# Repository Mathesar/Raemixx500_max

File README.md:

# Rämixx500_MAX

Rämixx500_MAX is an enhanced version of Sukkoperra's [Rämixx500](https://github.com/SukkoPera/Raemixx500), an Open Hardware remake of the Commodore Amiga 500+ mainboard, revision 8A.1.

## Features
The main feature of the Rämixx500_MAX compared to the original Rämixx500 is more RAM in the form of a 72pins 4Meg SIMM module that gives the Rämixx500_MAX 2Meg CHIP + 1.5Meg SLOW ram. Good working SIMM modules are much easier to source and more reliable than the DIP chips that were originally used in the A500+.

3.5 Megabytes of RAM is the maximum amount an A500+ can use without attaching an accelerator, hence the name Rämixx500_**MAX**.

All the new features of the Rämixx500_MAX are:

* **3.5 Megabytes of RAM**: Using a 72pin SIMM that is at least 4Meg in size.
* **Improved ESD Protection for the Joystick Ports**: The Rämixx500_MAX protects just the lines that go into the sensitive CIA and Paula chips but these lines are more rigorously protected by placing the ESD diodes right at the connectors.
* **Improved Hard Disk LED support**: This version accepts both active high and active low harddisk activity signals. Note that the active low harddisk activity LED input is only compatible with 5V devices. The active high harddisk activity LED input is compatible with both 3.3V and 5V devices.
* **Even more Accurate Dimensions**: The floppy port should fit slightly better. (It already was very, very close in the original Rämixx500 though)
* **Less jumpers**: With the SIMM module, one always has max RAM in all banks, no need to jump around with JP2, JP3 and JP4 anymore.

## Ordering parts and building (important)
Included with the gerbers is a BOM that contains most of the needed parts. Mouser part numbers are also included. 

The BOM and schematics reflect how I built my version. There are some options like buffered sync outputs and extra pullups that I did not use. If one wants these options then they will have to order the additional parts as well. 

Some more remarks regarding how I built my Rämixx500_MAX:

* I did not use sockets for all parts. I only used sockets for the second-hand / rare parts. All the standard logic IC's for example are not socketed. 
* For the 68000 the BOM specifies a high quality "machined" socket. This is done for reliable connection to a socketed accelerator. 
* The other sockets are standard "wiped" sockets. If one is planning to use, for example, an [A500_SD_PLUS](https://github.com/Mathesar/a500-sd-plus-controller) or a RGB2HDMI it is recommended to change the respective sockets (CIA / Denise) to machined sockets as well. This is because I have noticed that modern production wiped sockets get very loose if you insert something other that an IC in them.
* I have populated RP105, RP106 and RP107. This is unlike the original A500+ but these pullups help EPROM compatibility.
* In the BOM I have replaced the MC1488 and MC1489 with the functionally identical SN75C188N and SN75C189N.  
* In the BOM I have replaced the 74F139 with the CD74ACT139E.
* I did not populate the trapdoor connector P9 (not needed anymore).

Like said, the BOM will give you most of the parts needed. The missing parts are:

* **68000** (socket included in BOM)
* **Agnus** (socket included in BOM, only certain versions supported!)
* **Paula** (socket included in BOM)
* **Gary** (socket included in BOM)
* **Denise** (socket included in BOM)
* **2 CIA's** (socket included in BOM)
* **RTC U9** (socket included in BOM)
* **Trimmer capacitor TC-9** (for RTC)
* **Main oscillator X1** (PAL or NTSC)
* **Floppy DSUB connector**
* **Video DSUB connector**
* **Power connector**
* **SIMM module**
* **VIDIOT**

Any SIMM that is 4Meg or larger is supported. EDO and/or parity RAM is also supported.
There is one caveat though when using double-sided SIMM's. As the RTC chip is normally sitting in a socket it might interfere with the memory chips on the bottom of some SIMMs. All double-sided SIMMs I tested fitted but "your mileage may vary".
Also, The SIMM socket sticks out higher than the original DIP RAM chips. This can have implications for some accelerators or other add-ons that sit in the CPU socket. If one plans to use additional add-ons, please review carefully whether these will physically fit on the Rämixx500_MAX. Also see my remarks regarding IC sockets.

For the vidiot, one can use the [OpenAmigaVideoHybrid-04](https://github.com/Mathesar/OpenAmigaVideoHybrid-04) that I have also forked from Sukkoperra.

For further information I highly recommend reading [Sukkopera's wiki here](https://github.com/SukkoPera/Raemixx500/wiki/Assembly-and-Installation). Especially for important information regarding the correct Agnus version.

## Extras
I put my Rämixx500_MAX in a new case from [a1200.net](https://www.a1200.net/). 
For that I also needed a floppy drive so I modded a Sony MFP920 PC drive.
In the [extras](https://github.com/Mathesar/Raemixx500_max/tree/master/extras) folder in this repo one can find the FreeCad and STEP files for an eject button for this drive. I have also created an adapter that converts the Chinon eject button that comes with the a1200.net case to the Sony MFP920 drive. The Chinon eject button itself needs to be trimmed a bit on the back and then glued over the adapter.

## Releases
If one wants to get this board produced, one is recommended to get the latest release rather than the current git version, as the latter might be under development and is not guaranteed to be working.
The latest release also contains the BOM with Mouser part numbers and an interactive HTML BOM which is very helpful when populating the boards.

## Disclaimer
I have personally built and tested V3 of the Rämixx500_MAX. The current release is V3.1 that fixes some (very) minor issues. However, I have not built or tested V3.1 myself. So, build at your own risk.

## License
The Rämixx500_MAX inherits the license of the The Rämixx500 by SukkoPera as quoted below:

> The Rämixx500 documentation, including the design itself, is copyright &copy; SukkoPera 2019-2021 and is licensed under the [Creative Commons Attribution-NonCommercial-ShareAlike 4.0 International License](https://creativecommons.org/licenses/by-nc-sa/4.0/).
> 
> This documentation is distributed *as is* and WITHOUT ANY EXPRESS OR IMPLIED WARRANTIES whatsoever with respect to its functionality, operability or use, including, without limitation, any implied warranties OF MERCHANTABILITY, SATISFACTORY QUALITY, FITNESS FOR A PARTICULAR PURPOSE or infringement. We expressly disclaim any liability whatsoever for any direct, indirect, consequential, incidental or special damages, including, without limitation, lost revenues, lost profits, losses resulting from business interruption or loss of data, regardless of the form of action or legal theory under which the liability may be asserted, even if advised of the possibility or likelihood of such damages.
> 
> This said, I would like this project to progress further. **If anyone would like to do major work on it but is discouraged to do so by the impossibility to exploit the work commercially, please get in touch with me**, I will grant you a private license which will allow you to do that.

## Thanks
- Commodore, for making the coolest machine ever.
- [SukkoPera](https://github.com/SukkoPera) for creating the amazing Rämixx500 and making it open source. Without him this would have never been possible.
- [PeteAU](https://eab.abime.net/member.php?u=58900) for designing an A500 trapdoor RAM expansion and gary adapter. His design inspired me to give the Rämixx500_MAX some additional RAM.

## Pictures

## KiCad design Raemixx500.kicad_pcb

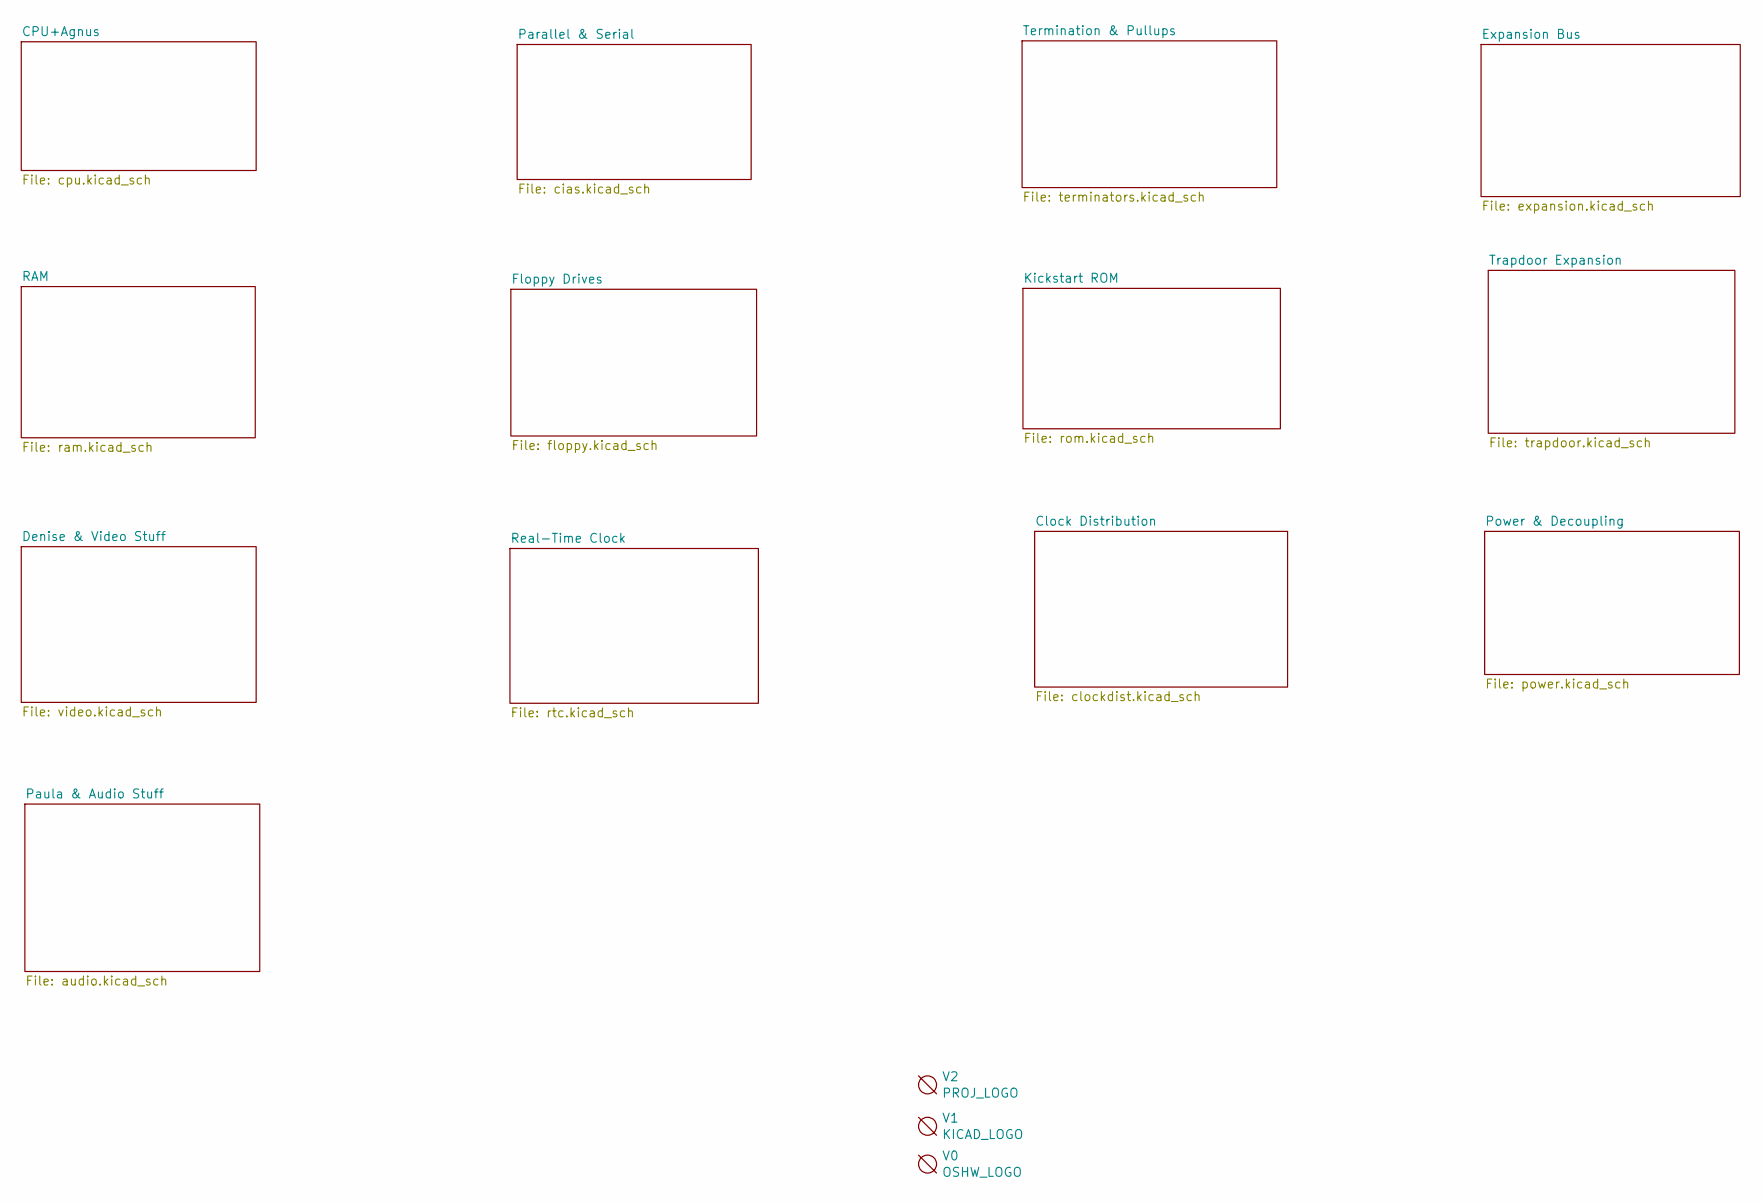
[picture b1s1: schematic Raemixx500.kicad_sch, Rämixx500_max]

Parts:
V0: OSHW_LOGO; cc_by_nc_sa; MFG Part Num SKIP
V1: KICAD_LOGO; KiCad-Logo2_6mm_SilkScreen; MFG Part Num SKIP
V2: PROJ_LOGO; logo_max; MFG Part Num SKIP

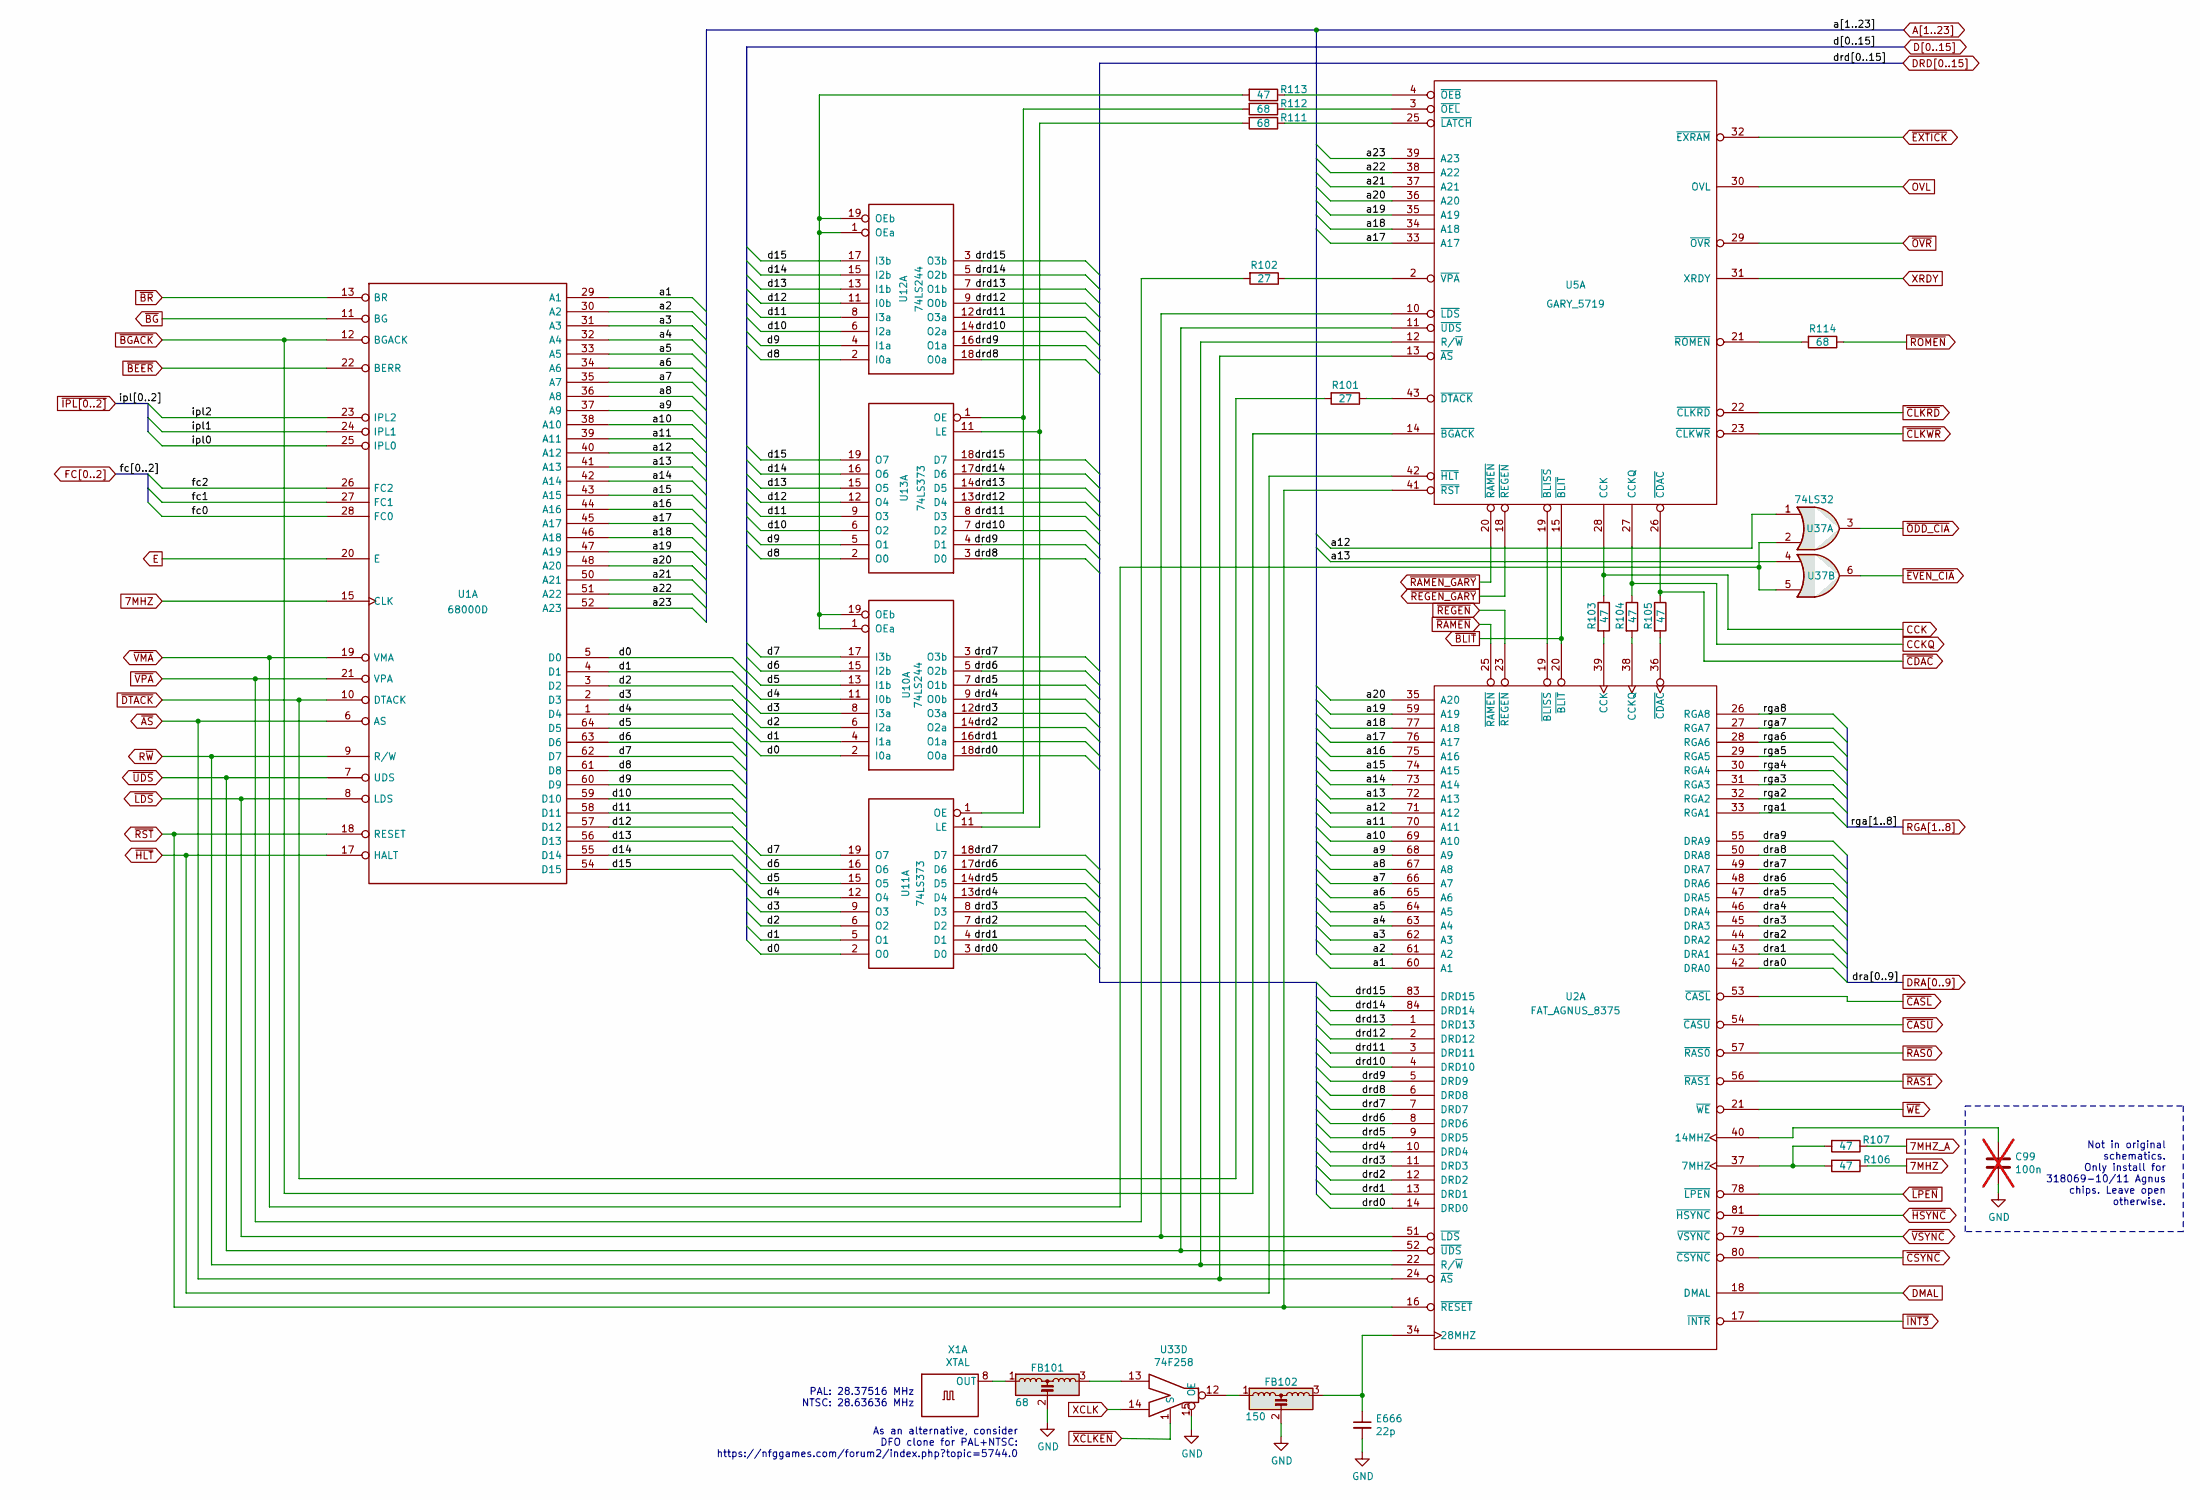
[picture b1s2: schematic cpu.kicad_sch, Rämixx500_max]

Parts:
C99: 100n; C_Axial_L6.3mm_D2.5mm_P10.16mm; MFG Part Num A104K15X7RF5TAA; Mouser 594-A104K15X7RF5TAA; not fitted
E666: 22p; C_Axial_L6.3mm_D2.5mm_P10.16mm; MFG Part Num C410C220J1G5TA; Mouser 80-C410C220J1G
FB101: 68; EMI_Filter_Long; MFG Part Num MFR-25FBF52-68R; Mouser 603-MFR-25FBF52-68R
FB102: 150; EMI_Filter_Long; MFG Part Num MFR-25FBF52-150R; Mouser 603-MFR-25FBF52-150R
R101, R102: 27; R_Axial_DIN0309_L9.0mm_D3.2mm_P12.70mm_Horizontal; MFG Part Num MFR-25FBF52-27R; Mouser 603-MFR-25FBF52-27R
R103, R104, R105, R106, R107, R113: 47; R_Axial_DIN0309_L9.0mm_D3.2mm_P12.70mm_Horizontal; MFG Part Num MFR-25FBF52-47R; Mouser 603-MFR-25FBF52-47R
R111, R112, R114: 68; R_Axial_DIN0309_L9.0mm_D3.2mm_P12.70mm_Horizontal; MFG Part Num MFR-25FBF52-68R; Mouser 603-MFR-25FBF52-68R
U1: 68000D; DIP-64_W22.86mm_Socket_LongPads; MFG Part Num 110-93-964-41-001000; Mouser 575-193964
U2: FAT_AGNUS_8375; PLCC-84_THT-Socket; MFG Part Num 940-44-084-24-000000; Mouser 575-948424
U5: GARY_5719; DIP-48_W15.24mm_Socket_LongPads; MFG Part Num 4848-6000-CP; Mouser 517-4848-6000-CP
U10, U12: 74LS244; DIP-20_W7.62mm_LongPads; MFG Part Num SN74LS244N; Mouser 595-SN74LS244N
U11, U13: 74LS373; DIP-20_W7.62mm_LongPads; MFG Part Num SN74LS373N; Mouser 595-SN74LS373N
U33: 74F258; DIP-16_W7.62mm_LongPads; MFG Part Num SN74F258N; Mouser 595-SN74F258N
U37: 74LS32; DIP-14_W7.62mm_LongPads; MFG Part Num SN74LS32N; Mouser 595-SN74LS32N
X1: XTAL; Oscillator_DIP-14

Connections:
7MHZ: R106.1, U1.15 (CLK); also elsewhere on the board
7MHZ_A: R107.1; also elsewhere on the board
A1: U1.29 (A1), U2.60 (A1); also elsewhere on the board
A2: U1.30 (A2), U2.61 (A2); also elsewhere on the board
A3: U1.31 (A3), U2.62 (A3); also elsewhere on the board
A4: U1.32 (A4), U2.63 (A4); also elsewhere on the board
A5: U1.33 (A5), U2.64 (A5); also elsewhere on the board
A6: U1.34 (A6), U2.65 (A6); also elsewhere on the board
A7: U1.35 (A7), U2.66 (A7); also elsewhere on the board
A8: U1.36 (A8), U2.67 (A8); also elsewhere on the board
A9: U1.37 (A9), U2.68 (A9); also elsewhere on the board
A10: U1.38 (A10), U2.69 (A10); also elsewhere on the board
A11: U1.39 (A11), U2.70 (A11); also elsewhere on the board
A12: U1.40 (A12), U2.71 (A12), U37.1; also elsewhere on the board
A13: U1.41 (A13), U2.72 (A13), U37.4; also elsewhere on the board
A14: U1.42 (A14), U2.73 (A14); also elsewhere on the board
A15: U1.43 (A15), U2.74 (A15); also elsewhere on the board
A16: U1.44 (A16), U2.75 (A16); also elsewhere on the board
A17: U1.45 (A17), U2.76 (A17), U5.33 (A17); also elsewhere on the board
A18: U1.46 (A18), U2.77 (A18), U5.34 (A18); also elsewhere on the board
A19: U1.47 (A19), U2.59 (A19), U5.35 (A19); also elsewhere on the board
A20: U1.48 (A20), U2.35 (A20), U5.36 (A20); also elsewhere on the board
A21: U1.50 (A21), U5.37 (A21); also elsewhere on the board
A22: U1.51 (A22), U5.38 (A22); also elsewhere on the board
A23: U1.52 (A23), U5.39 (A23); also elsewhere on the board
CCK: R103.1, U5.28 (CCK); also elsewhere on the board
CCKQ: R104.1, U5.27 (CCKQ); also elsewhere on the board
D0: U1.5 (D0), U10.2 (I0a), U11.2 (O0); also elsewhere on the board
D1: U1.4 (D1), U10.4 (I1a), U11.5 (O1); also elsewhere on the board
D2: U1.3 (D2), U10.6 (I2a), U11.6 (O2); also elsewhere on the board
D3: U1.2 (D3), U10.8 (I3a), U11.9 (O3); also elsewhere on the board
D4: U1.1 (D4), U10.11 (I0b), U11.12 (O4); also elsewhere on the board
D5: U1.64 (D5), U10.13 (I1b), U11.15 (O5); also elsewhere on the board
D6: U1.63 (D6), U10.15 (I2b), U11.16 (O6); also elsewhere on the board
D7: U1.62 (D7), U10.17 (I3b), U11.19 (O7); also elsewhere on the board
D8: U1.61 (D8), U12.2 (I0a), U13.2 (O0); also elsewhere on the board
D9: U1.60 (D9), U12.4 (I1a), U13.5 (O1); also elsewhere on the board
D10: U1.59 (D10), U12.6 (I2a), U13.6 (O2); also elsewhere on the board
D11: U1.58 (D11), U12.8 (I3a), U13.9 (O3); also elsewhere on the board
D12: U1.57 (D12), U12.11 (I0b), U13.12 (O4); also elsewhere on the board
D13: U1.56 (D13), U12.13 (I1b), U13.15 (O5); also elsewhere on the board
D14: U1.55 (D14), U12.15 (I2b), U13.16 (O6); also elsewhere on the board
D15: U1.54 (D15), U12.17 (I3b), U13.19 (O7); also elsewhere on the board
DMAL: U2.18 (DMAL); also elsewhere on the board
DRA0: U2.42 (DRA0); also elsewhere on the board
DRA1: U2.43 (DRA1); also elsewhere on the board
DRA2: U2.44 (DRA2); also elsewhere on the board
DRA3: U2.45 (DRA3); also elsewhere on the board
DRA4: U2.46 (DRA4); also elsewhere on the board
DRA5: U2.47 (DRA5); also elsewhere on the board
DRA6: U2.48 (DRA6); also elsewhere on the board
DRA7: U2.49 (DRA7); also elsewhere on the board
DRA8: U2.50 (DRA8); also elsewhere on the board
DRA9: U2.55 (DRA9); also elsewhere on the board
DRD0: U2.14 (DRD0), U10.18 (O0a), U11.3 (D0); also elsewhere on the board
DRD1: U2.13 (DRD1), U10.16 (O1a), U11.4 (D1); also elsewhere on the board
DRD2: U2.12 (DRD2), U10.14 (O2a), U11.7 (D2); also elsewhere on the board
DRD3: U2.11 (DRD3), U10.12 (O3a), U11.8 (D3); also elsewhere on the board
DRD4: U2.10 (DRD4), U10.9 (O0b), U11.13 (D4); also elsewhere on the board
DRD5: U2.9 (DRD5), U10.7 (O1b), U11.14 (D5); also elsewhere on the board
DRD6: U2.8 (DRD6), U10.5 (O2b), U11.17 (D6); also elsewhere on the board
DRD7: U2.7 (DRD7), U10.3 (O3b), U11.18 (D7); also elsewhere on the board
DRD8: U2.6 (DRD8), U12.18 (O0a), U13.3 (D0); also elsewhere on the board
DRD9: U2.5 (DRD9), U12.16 (O1a), U13.4 (D1); also elsewhere on the board
DRD10: U2.4 (DRD10), U12.14 (O2a), U13.7 (D2); also elsewhere on the board
DRD11: U2.3 (DRD11), U12.12 (O3a), U13.8 (D3); also elsewhere on the board
DRD12: U2.2 (DRD12), U12.9 (O0b), U13.13 (D4); also elsewhere on the board
DRD13: U2.1 (DRD13), U12.7 (O1b), U13.14 (D5); also elsewhere on the board
DRD14: U2.84 (DRD14), U12.5 (O2b), U13.17 (D6); also elsewhere on the board
DRD15: U2.83 (DRD15), U12.3 (O3b), U13.18 (D7); also elsewhere on the board
E: U1.20 (E); also elsewhere on the board
FC0: U1.28 (FC0); also elsewhere on the board
FC1: U1.27 (FC1); also elsewhere on the board
FC2: U1.26 (FC2); also elsewhere on the board
GND: C99.2, E666.2, FB101.2, FB102.2, U33.15 (OE); also elsewhere on the board
unnamed: FB101.3, U33.13
unnamed: FB102.1, U33.12
unnamed: R106.2, R107.2, U2.37 (7MHZ)
unnamed: C99.1, U2.40 (14MHZ)
unnamed: E666.1, FB102.3, U2.34 (28MHZ)
unnamed: R103.2, U2.39 (CCK)
unnamed: R104.2, U2.38 (CCKQ)
unnamed: U2.19 (~BLISS), U5.19 (~BLISS)
unnamed: R105.2, U2.36 (~CDAC)
unnamed: R101.1, U5.43 (~DTACK)
unnamed: R111.1, U5.25 (~LATCH)
unnamed: R113.1, U5.4 (~OEB)
unnamed: R112.1, U5.3 (~OEL)
unnamed: R114.2, U5.21 (~ROMEN)
unnamed: R102.1, U5.2 (~VPA)
unnamed: R113.2, U10.1 (OEa), U10.19 (OEb), U12.1 (OEa), U12.19 (OEb)
unnamed: R111.2, U11.11 (LE), U13.11 (LE)
unnamed: R112.2, U11.1 (OE), U13.1 (OE)
unnamed: FB101.1, X1.8 (OUT)
OVL: U5.30 (OVL); also elsewhere on the board
RGA1: U2.33 (RGA1); also elsewhere on the board
RGA2: U2.32 (RGA2); also elsewhere on the board
RGA3: U2.31 (RGA3); also elsewhere on the board
RGA4: U2.30 (RGA4); also elsewhere on the board
RGA5: U2.29 (RGA5); also elsewhere on the board
RGA6: U2.28 (RGA6); also elsewhere on the board
RGA7: U2.27 (RGA7); also elsewhere on the board
RGA8: U2.26 (RGA8); also elsewhere on the board
R~W: U1.9 (R/W), U2.22 (R/~W), U5.12 (R/~W); also elsewhere on the board
XCLK: U33.14; also elsewhere on the board
XRDY: U5.31 (XRDY); also elsewhere on the board
~AS: U1.6 (AS), U2.24 (~AS), U5.13 (~AS); also elsewhere on the board
~BEER: U1.22 (BERR); also elsewhere on the board
~BGACK: U1.12 (BGACK), U5.14 (~BGACK); also elsewhere on the board
~BG: U1.11 (BG); also elsewhere on the board
~BLIT: U2.20 (~BLIT), U5.15 (~BLIT); also elsewhere on the board
~BR: U1.13 (BR); also elsewhere on the board
~CASL: U2.53 (~CASL); also elsewhere on the board
~CASU: U2.54 (~CASU); also elsewhere on the board
~CDAC: R105.1, U5.26 (~CDAC); also elsewhere on the board
~CLKRD: U5.22 (~CLKRD); also elsewhere on the board
~CLKWR: U5.23 (~CLKWR); also elsewhere on the board
~CSYNC: U2.80 (~CSYNC); also elsewhere on the board
~DTACK: R101.2, U1.10 (DTACK); also elsewhere on the board
~EVEN_CIA: U37.6; also elsewhere on the board
~EXTICK: U5.32 (~EXRAM); also elsewhere on the board
~HLT: U1.17 (HALT), U5.42 (~HLT); also elsewhere on the board
~HSYNC: U2.81 (~HSYNC); also elsewhere on the board
~INT3: U2.17 (~INTR); also elsewhere on the board
~IPL0: U1.25 (IPL0); also elsewhere on the board
~IPL1: U1.24 (IPL1); also elsewhere on the board
~IPL2: U1.23 (IPL2); also elsewhere on the board
~LDS: U1.8 (LDS), U2.51 (~LDS), U5.10 (~LDS); also elsewhere on the board
~LPEN: U2.78 (~LPEN); also elsewhere on the board
~ODD_CIA: U37.3; also elsewhere on the board
~OVR: U5.29 (~OVR); also elsewhere on the board
~RAMEN_GARY: U5.20 (~RAMEN); also elsewhere on the board
~RAMEN: U2.25 (~RAMEN); also elsewhere on the board
~RAS0: U2.57 (~RAS0); also elsewhere on the board
~RAS1: U2.56 (~RAS1); also elsewhere on the board
~REGEN_GARY: U5.18 (~REGEN); also elsewhere on the board
~REGEN: U2.23 (~REGEN); also elsewhere on the board
~ROMEN: R114.1; also elsewhere on the board
~RST: U1.18 (RESET), U2.16 (~RESET), U5.41 (~RST); also elsewhere on the board
~UDS: U1.7 (UDS), U2.52 (~UDS), U5.11 (~UDS); also elsewhere on the board
~VMA: U1.19 (VMA), U37.2, U37.5; also elsewhere on the board
~VPA: R102.2, U1.21 (VPA); also elsewhere on the board
~VSYNC: U2.79 (~VSYNC); also elsewhere on the board
~WE: U2.21 (~WE); also elsewhere on the board
~XCLKEN: U33.1 (S); also elsewhere on the board

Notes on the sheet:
PAL: 28.37516 MHz NTSC: 28.63636 MHz
As an alternative, consider DFO clone for PAL+NTSC: https://nfggames.com/forum2/index.php?topic=5744.0
Not in original schematics. Only install for 318069-10/11 Agnus chips. Leave open otherwise.

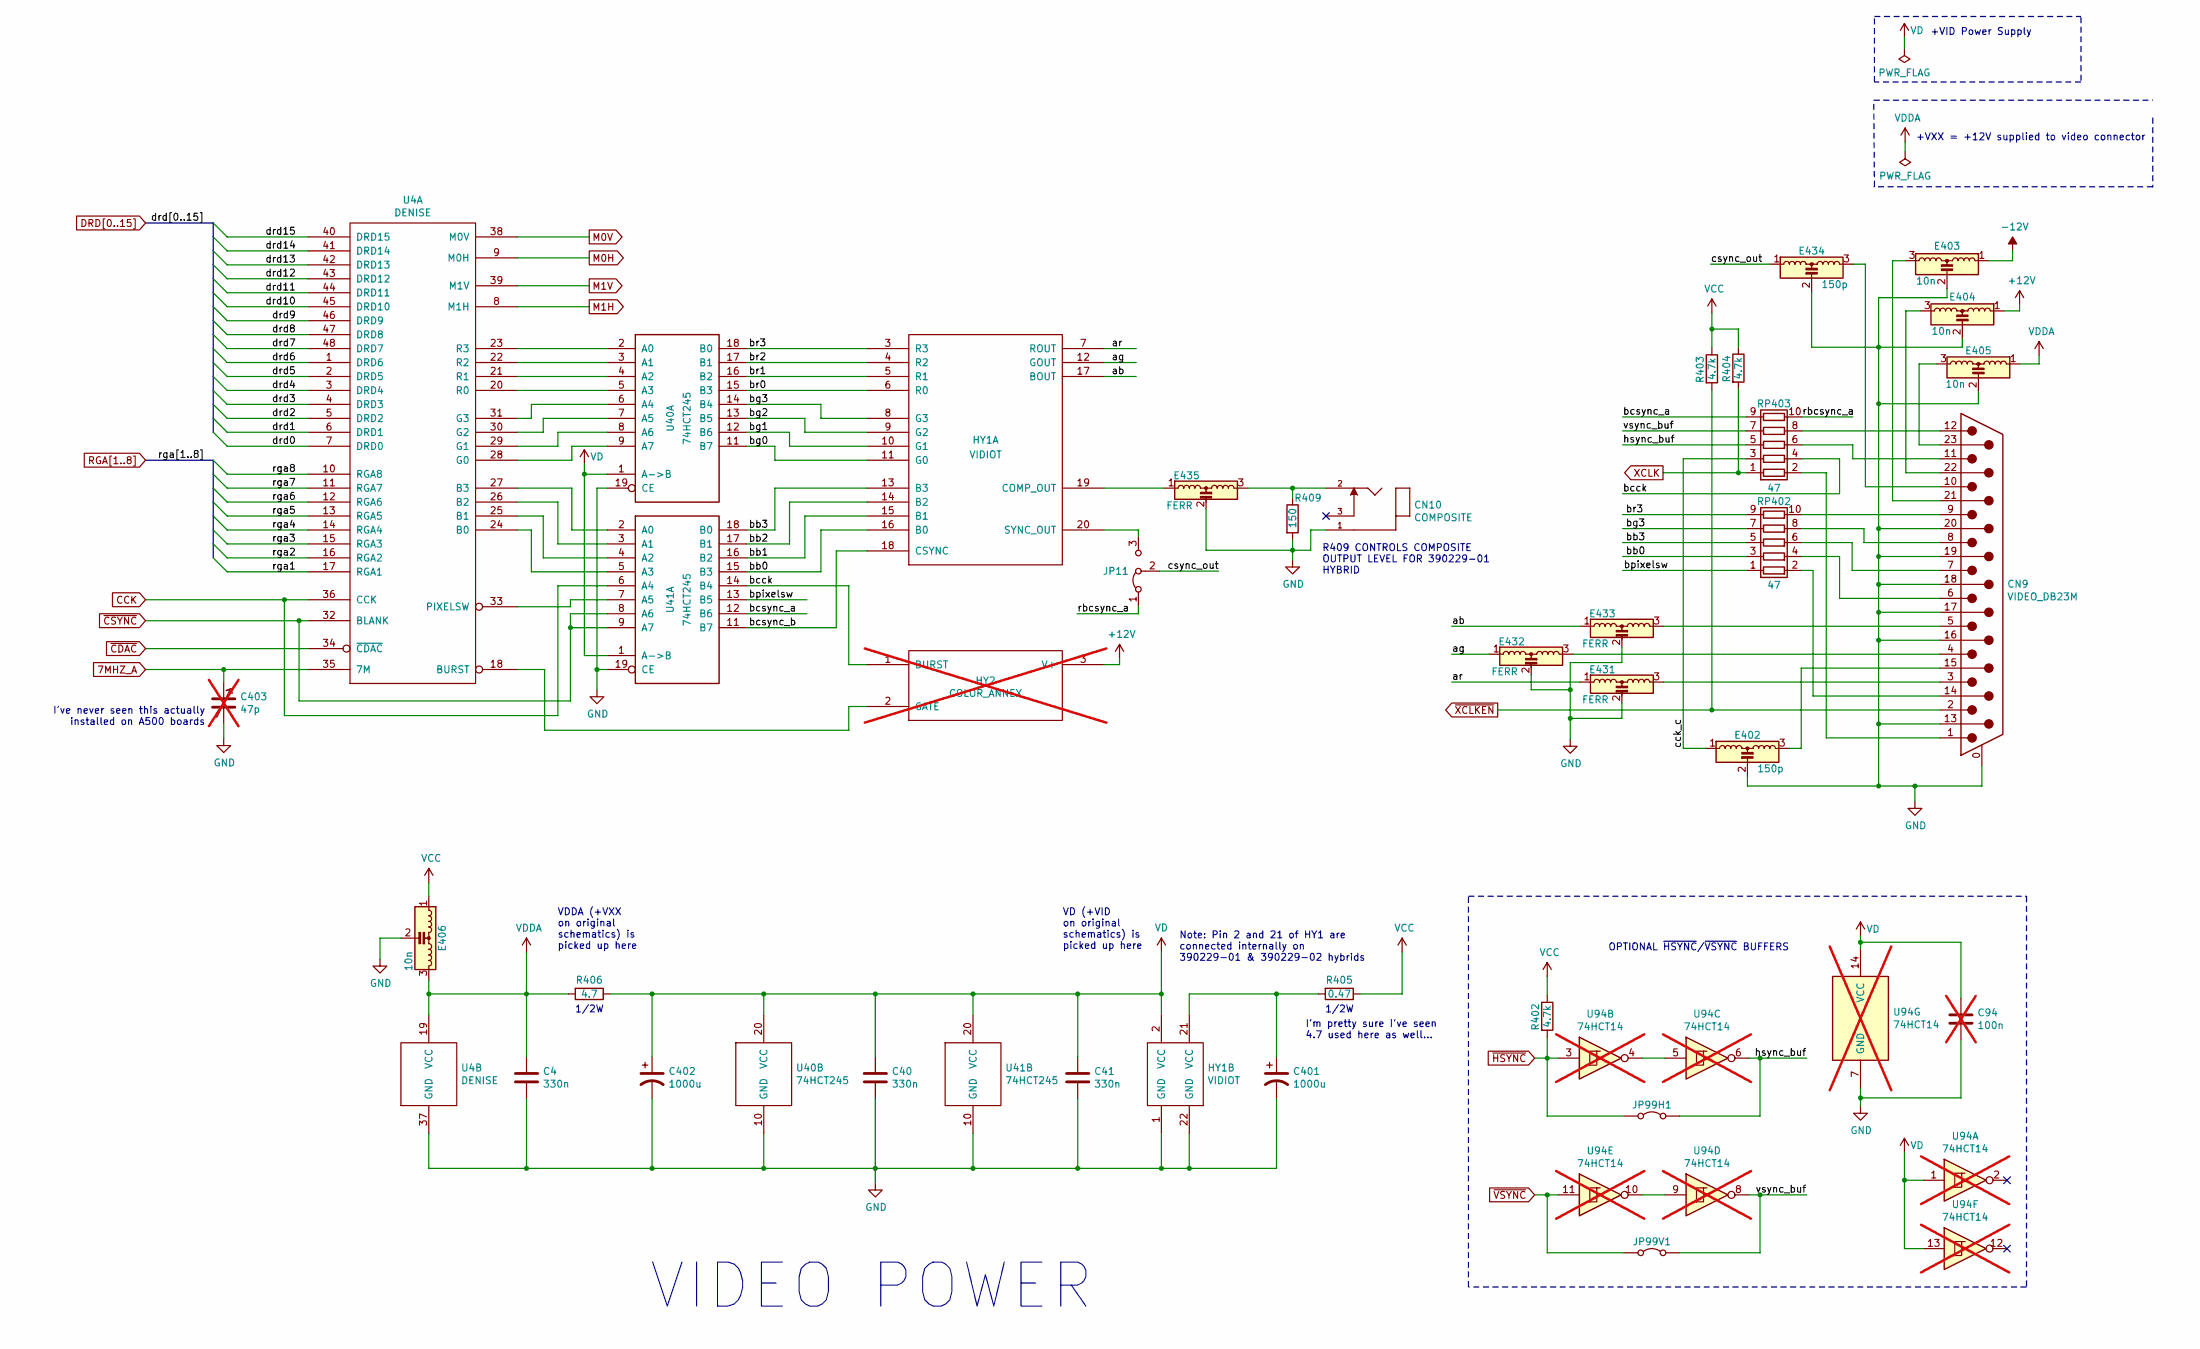
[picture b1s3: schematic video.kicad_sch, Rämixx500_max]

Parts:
C4, C40, C41: 330n; C_Axial_L6.3mm_D2.5mm_P10.16mm; MFG Part Num C440C334K5R5TA7200; Mouser 80-C440C334K5R-TR
C94: 100n; C_Axial_L6.3mm_D2.5mm_P10.16mm; MFG Part Num A104K15X7RF5TAA; Mouser 594-A104K15X7RF5TAA; not fitted
C401, C402: 1000u; CP_Radial_D12.5mm_P5.00mm; MFG Part Num ECA-1EM102; Mouser 667-ECA-1EM102
C403: 47p; VariCap; MFG Part Num SKIP; not fitted
CN9: VIDEO_DB23M; DB_23M; MFG Part Num 390242-03
CN10: COMPOSITE; SWITCHCRAFT_PJRAN1X1U01X; MFG Part Num PJRAN1X1U01AUX; Mouser 502-PJRAN1X1U01AUX
E402, E434: 150p; EMI_Filter_Long; MFG Part Num DSS1NB32A151Q91A; Mouser 81-DSS1NB32A151Q91A
E403, E404, E405: 10n; EMI_Filter_Long; MFG Part Num DSS1NB32A103Q91A; Mouser 81-DSS1NB32A103Q91A
E406: 10n; EMI_Filter_Short; MFG Part Num DSS1NB32A103Q91A; Mouser 81-DSS1NB32A103Q91A
E431, E432, E433, E435: FERR; EMI_Filter_Long; MFG Part Num ALFB-02; Mouser 815-ALFB-02
HY1: VIDIOT; PinHeader_1x22_P2.54mm_Vertical; MFG Part Num OpenAmigaVideoHybrid-04
HY2: COLOR_ANNEX; PinHeader_1x03_P2.54mm_Vertical; MFG Part Num SKIP; not fitted
JP11: Jumper_3_Bridged12; Jumper3-Bridged12; MFG Part Num SKIP
JP99H1, JP99V1: Jumper_2_Bridged; Jumper2-Bridged; MFG Part Num SKIP
R402, R403, R404: 4.7k; R_Axial_DIN0309_L9.0mm_D3.2mm_P12.70mm_Horizontal; MFG Part Num MFR-25FBF52-4K7; Mouser 603-MFR-25FBF52-4K7
R405: 0.47; R_Axial_DIN0309_L9.0mm_D3.2mm_P15.24mm_Horizontal; MFG Part Num PR01000104707JA500; Mouser 594-PR01000104707JA5
R406: 4.7; R_Axial_DIN0309_L9.0mm_D3.2mm_P15.24mm_Horizontal; MFG Part Num PR01000104708JA500; Mouser 594-PR01000104708JA5
R409: 150; R_Axial_DIN0309_L9.0mm_D3.2mm_P12.70mm_Horizontal; MFG Part Num MFR-25FBF52-150R; Mouser 603-MFR-25FBF52-150R
RP402, RP403: 47; R_Array_SIP10; MFG Part Num 4610X-102-470LF; Mouser 652-4610X-2LF-47
U4: DENISE; DIP-48_W15.24mm_Socket_LongPads; MFG Part Num 4848-6000-CP; Mouser 517-4848-6000-CP
U40, U41: 74HCT245; DIP-20_W7.62mm_LongPads; MFG Part Num SN74HCT245N; Mouser 595-SN74HCT245N
U94: 74HCT14; SOIC-14_3.9x8.7mm_P1.27mm; not fitted

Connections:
7MHZ_A: C403.1, U4.35 (7M); also elsewhere on the board
+12V: E404.1, HY2.3 (V+); also elsewhere on the board
-12V: E403.1; also elsewhere on the board
/Denise & Video Stuff/ab: E433.1, HY1.17 (BOUT)
/Denise & Video Stuff/ag: E432.1, HY1.12 (GOUT)
/Denise & Video Stuff/ar: E431.1, HY1.7 (ROUT)
/Denise & Video Stuff/bb0: HY1.16 (B0), RP402.3 (R2.1), U41.15 (B3)
/Denise & Video Stuff/bb1: HY1.15 (B1), U41.16 (B2)
/Denise & Video Stuff/bb2: HY1.14 (B2), U41.17 (B1)
/Denise & Video Stuff/bb3: HY1.13 (B3), RP402.5 (R3.1), U41.18 (B0)
/Denise & Video Stuff/bcck: HY2.1 (BURST), RP403.4 (R2.2), U41.14 (B4)
/Denise & Video Stuff/bcsync_a: RP403.9 (R5.1), U41.12 (B6)
/Denise & Video Stuff/bcsync_b: HY1.18 (CSYNC), U41.11 (B7)
/Denise & Video Stuff/bg0: HY1.11 (G0), U40.11 (B7)
/Denise & Video Stuff/bg1: HY1.10 (G1), U40.12 (B6)
/Denise & Video Stuff/bg2: HY1.9 (G2), U40.13 (B5)
/Denise & Video Stuff/bg3: HY1.8 (G3), RP402.7 (R4.1), U40.14 (B4)
/Denise & Video Stuff/bpixelsw: RP402.1 (R1.1), U41.13 (B5)
/Denise & Video Stuff/br0: HY1.6 (R0), U40.15 (B3)
/Denise & Video Stuff/br1: HY1.5 (R1), U40.16 (B2)
/Denise & Video Stuff/br2: HY1.4 (R2), U40.17 (B1)
/Denise & Video Stuff/br3: HY1.3 (R3), RP402.9 (R5.1), U40.18 (B0)
/Denise & Video Stuff/cck_c: E402.1, RP403.3 (R2.1)
/Denise & Video Stuff/csync_out: E434.1, JP11.2 (C)
/Denise & Video Stuff/hsync_buf: JP99H1.2 (B), RP403.5 (R3.1), U94.6
/Denise & Video Stuff/rbcsync_a: JP11.1 (A), RP403.10 (R5.2)
/Denise & Video Stuff/vsync_buf: JP99V1.2 (B), RP403.7 (R4.1), U94.8
CCK: U4.36 (CCK), U41.6 (A4); also elsewhere on the board
DRD0: U4.7 (DRD0); also elsewhere on the board
DRD1: U4.6 (DRD1); also elsewhere on the board
DRD2: U4.5 (DRD2); also elsewhere on the board
DRD3: U4.4 (DRD3); also elsewhere on the board
DRD4: U4.3 (DRD4); also elsewhere on the board
DRD5: U4.2 (DRD5); also elsewhere on the board
DRD6: U4.1 (DRD6); also elsewhere on the board
DRD7: U4.48 (DRD7); also elsewhere on the board
DRD8: U4.47 (DRD8); also elsewhere on the board
DRD9: U4.46 (DRD9); also elsewhere on the board
DRD10: U4.45 (DRD10); also elsewhere on the board
DRD11: U4.44 (DRD11); also elsewhere on the board
DRD12: U4.43 (DRD12); also elsewhere on the board
DRD13: U4.42 (DRD13); also elsewhere on the board
DRD14: U4.41 (DRD14); also elsewhere on the board
DRD15: U4.40 (DRD15); also elsewhere on the board
GND: C4.2, C40.2, C41.2, C94.2, C401.2, C402.2, C403.2, CN9.0 (PAD), CN9.13, CN9.16, CN9.17, CN9.18, CN9.19, CN9.20, CN10.1, E402.2, E403.2, E404.2, E405.2, E406.2, E431.2, E432.2, E433.2, E434.2, E435.2, HY1.1 (GND), HY1.22 (GND), R409.2, U4.37 (GND), U40.10 (GND), U40.19 (CE), U41.10 (GND), U41.19 (CE), U94.7 (GND); also elsewhere on the board
M0H: U4.9 (M0H); also elsewhere on the board
M0V: U4.38 (M0V); also elsewhere on the board
M1H: U4.8 (M1H); also elsewhere on the board
M1V: U4.39 (M1V); also elsewhere on the board
unnamed: C401.1, HY1.21 (VCC), R405.2
unnamed: CN9.14, RP402.2 (R1.2)
unnamed: CN9.15, E402.3
unnamed: CN9.21, E403.3
unnamed: CN9.22, E404.3
unnamed: CN9.23, E405.3
unnamed: CN9.3, E431.3
unnamed: CN9.4, E432.3
unnamed: CN9.5, E433.3
unnamed: CN9.10, E434.3
unnamed: CN10.2, E435.3, R409.1
unnamed: E435.1, HY1.19 (COMP_OUT)
unnamed: HY1.20 (SYNC_OUT), JP11.3 (B)
unnamed: HY2.2 (GATE), U4.18 (BURST)
unnamed: CN9.6, RP402.4 (R2.2)
unnamed: CN9.7, RP402.6 (R3.2)
unnamed: CN9.8, RP402.8 (R4.2)
unnamed: CN9.9, RP402.10 (R5.2)
unnamed: CN9.1, RP403.2 (R1.2)
unnamed: CN9.11, RP403.6 (R3.2)
unnamed: CN9.12, RP403.8 (R4.2)
unnamed: U4.23 (R3), U40.2 (A0)
unnamed: U4.22 (R2), U40.3 (A1)
unnamed: U4.21 (R1), U40.4 (A2)
unnamed: U4.20 (R0), U40.5 (A3)
unnamed: U4.31 (G3), U40.6 (A4)
unnamed: U4.30 (G2), U40.7 (A5)
unnamed: U4.29 (G1), U40.8 (A6)
unnamed: U4.28 (G0), U40.9 (A7)
unnamed: U4.27 (B3), U41.2 (A0)
unnamed: U4.26 (B2), U41.3 (A1)
unnamed: U4.25 (B1), U41.4 (A2)
unnamed: U4.24 (B0), U41.5 (A3)
unnamed: U4.33 (PIXELSW), U41.7 (A5)
unnamed: U94.4, U94.5
unnamed: U94.9, U94.10
RGA1: U4.17 (RGA1); also elsewhere on the board
RGA2: U4.16 (RGA2); also elsewhere on the board
RGA3: U4.15 (RGA3); also elsewhere on the board
RGA4: U4.14 (RGA4); also elsewhere on the board
RGA5: U4.13 (RGA5); also elsewhere on the board
RGA6: U4.12 (RGA6); also elsewhere on the board
RGA7: U4.11 (RGA7); also elsewhere on the board
RGA8: U4.10 (RGA8); also elsewhere on the board
VCC: E406.1, R402.1, R403.1, R404.1, R405.1; also elsewhere on the board
VD: C40.1, C41.1, C94.1, C402.1, HY1.2 (VCC), R406.1, U40.1 (A->B), U40.20 (VCC), U41.1 (A->B), U41.20 (VCC), U94.1, U94.13, U94.14 (VCC)
VDDA: C4.1, E405.1, E406.3, R406.2, U4.19 (VCC)
XCLK: R404.2, RP403.1 (R1.1); also elsewhere on the board
~CDAC: U4.34 (~CDAC); also elsewhere on the board
~CSYNC: U4.32 (BLANK), U41.8 (A6), U41.9 (A7); also elsewhere on the board
~HSYNC: JP99H1.1 (A), R402.2, U94.3; also elsewhere on the board
~VSYNC: JP99V1.1 (A), U94.11; also elsewhere on the board
~XCLKEN: CN9.2, R403.2; also elsewhere on the board

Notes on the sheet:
VIDEO POWER
VD (+VID on original schematics) is picked up here
1/2W
VDDA (+VXX on original schematics) is picked up here
+VXX = +12V supplied to video connector
+VID Power Supply
Note: Pin 2 and 21 of HY1 are connected internally on 390229-01 & 390229-02 hybrids
OPTIONAL ~{HSYNC}/~{VSYNC} BUFFERS
I'm pretty sure I've seen 4.7 used here as well...
R409 CONTROLS COMPOSITE OUTPUT LEVEL FOR 390229-01 HYBRID
I've never seen this actually installed on A500 boards

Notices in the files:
Raemixx500.kicad_pcb:
Licensed under CC BY-NC-SA 4.0
